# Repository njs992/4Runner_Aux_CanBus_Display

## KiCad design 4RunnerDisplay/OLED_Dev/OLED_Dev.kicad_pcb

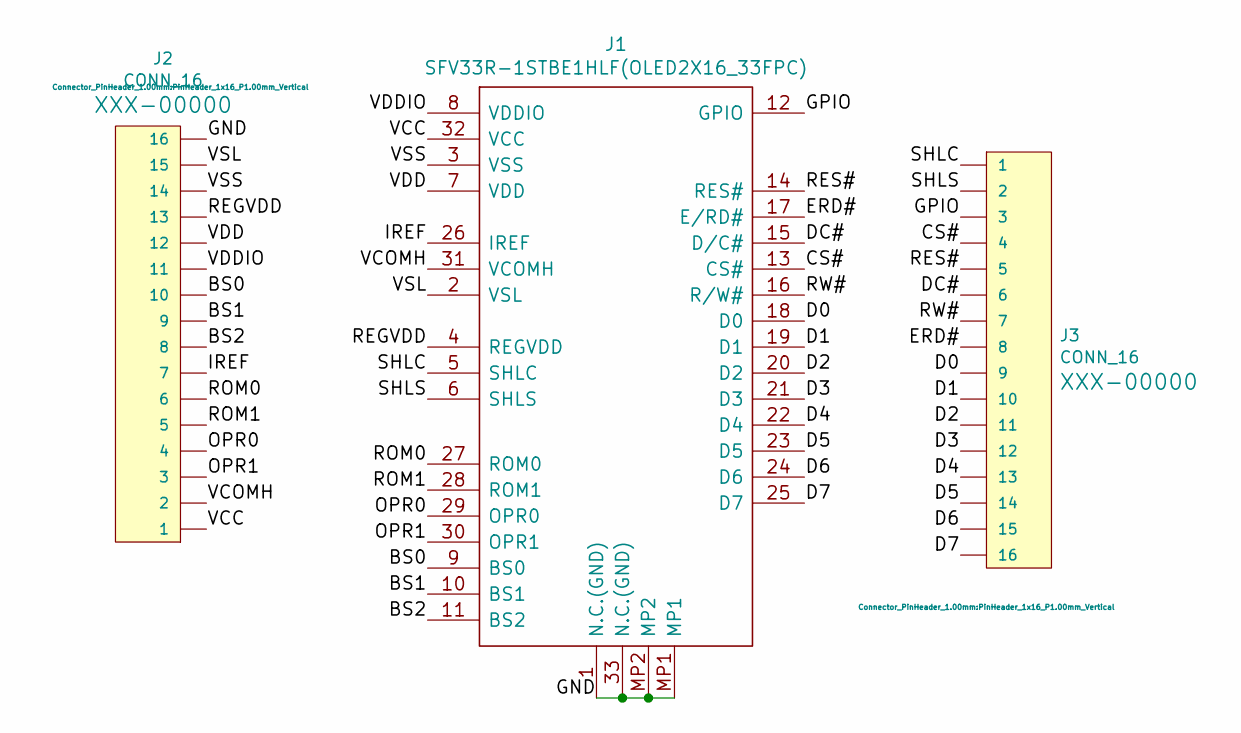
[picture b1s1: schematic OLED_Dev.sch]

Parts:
J1: SFV33R-1STBE1HLF(OLED2X16_33FPC); SFV33R1STBE1HLF; Mouser Part Number 649-SFV33R-1STBE1HLF
J2, J3: CONN_16; PinHeader_1x16_P1.00mm_Vertical

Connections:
/BS0: J1.9 (BS0), J2.10
/BS1: J1.10 (BS1), J2.9
/BS2: J1.11 (BS2), J2.8
/CS#: J1.13 (CS#), J3.4
/D0: J1.18 (D0), J3.9
/D1: J1.19 (D1), J3.10
/D2: J1.20 (D2), J3.11
/D3: J1.21 (D3), J3.12
/D4: J1.22 (D4), J3.13
/D5: J1.23 (D5), J3.14
/D6: J1.24 (D6), J3.15
/D7: J1.25 (D7), J3.16
/DC#: J1.15 (D/C#), J3.6
/ERD#: J1.17 (E/RD#), J3.8
/GND: J1.1 (N.C.(GND)), J1.33 (N.C.(GND)), J1.MP1, J1.MP2, J2.16
/GPIO: J1.12 (GPIO), J3.3
/IREF: J1.26 (IREF), J2.7
/OPR0: J1.29 (OPR0), J2.4
/OPR1: J1.30 (OPR1), J2.3
/REGVDD: J1.4 (REGVDD), J2.13
/RES#: J1.14 (RES#), J3.5
/ROM0: J1.27 (ROM0), J2.6
/ROM1: J1.28 (ROM1), J2.5
/RW#: J1.16 (R/W#), J3.7
/SHLC: J1.5 (SHLC), J3.1
/SHLS: J1.6 (SHLS), J3.2
/VCC: J1.32 (VCC), J2.1
/VCOMH: J1.31 (VCOMH), J2.2
/VDD: J1.7 (VDD), J2.12
/VDDIO: J1.8 (VDDIO), J2.11
/VSL: J1.2 (VSL), J2.15
/VSS: J1.3 (VSS), J2.14

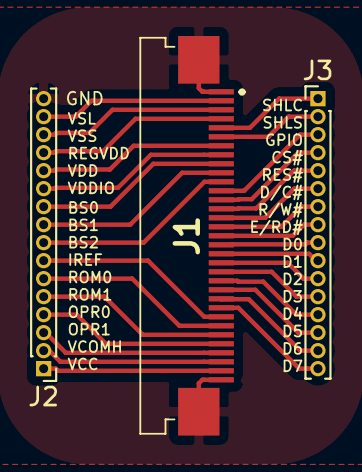
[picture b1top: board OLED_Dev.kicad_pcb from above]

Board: 2 copper layers, 3 parts (0 on the bottom side), 32 nets.

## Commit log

2019-09-20 1996 Toyota 4Runner Auxillary Display
